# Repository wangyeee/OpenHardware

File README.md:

# OpenHardware
Collections of hardware design related to my drone project.

Brief description for each folders.

| Folder | Description | CAD software |
|---|---|---|
| CurrentMonitor | A simple [ACS758](https://www.allegromicro.com/en/Products/Current-Sensor-ICs/Fifty-To-Two-Hundred-Amp-Integrated-Conductor-Sensor-ICs/ACS758.aspx) breakout board | EAGLE |
| LoRaModem | A board with [Ra-02](http://wiki.ai-thinker.com/_media/lora/docs/c048ps01a1_ra-02_product_specification_v1.1.pdf) LoRa Module and [STM32](https://www.st.com/en/microcontrollers/stm32f103cb.html) MCU | KiCAD |
| OscillatorBreakout | A breakout board for oscillators, supporting three different oscillator packages | KiCAD |
| SimpleFC | Simple yet powerful flight controller for drones, capable of fully autonomous GPS navigation | KiCAD |
| SimpleFCv2 | Version 2 of SimpleFC, with reduced PCB size | KiCAD |
| SimpleFC_G | SimpleFCv2 with integrated GPS receiver | KiCAD |
| MultiRotorHub | A support board in multi-rotor which makes cable management easy | EAGLE |
| PowerModule  | 2s ~ 6s Li-Po BEC with current monitoring |EAGLE  |
| SerialBTBridge | A bridge board between RFM22B telemetry module and HC05 Bluetooth module | EAGLE |
| TinyFC | A tiny flight controller module, supporting board stacking for advanced features | KiCAD |
| ReflowOvenController | A controller board used to convert a commercial oven to PCB reflow oven. | KiCAD |
| AirSensor | A barometer and differential pressure sensor board with UAVCAN support. | KiCAD |
| DIYDummyLoad | A primitive DC dummy load with STM32F103. | EAGLE |
| TinyBEC | 2s ~ 3s / 2A Li-Po BEC, board size 23x18mm. | KiCAD |

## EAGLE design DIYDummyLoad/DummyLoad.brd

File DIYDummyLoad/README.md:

# DIYDummyLoad
A primitive DC dummy load with STM32F103. Firmware is also open source and can be found in this [repo](https://github.com/wangyeee/DIYDummyLoad).

## Components & features
1. STM32F103RC MCU.
2. LMV321 OpAmp and IRFB3607PBF N-channel MOSFET for the load.
3. LMV324 as input buffer for the STM32 ADC.
4. ILI9163C LCD.
5. Rotatory encoder to set parameters.
6. Connector for external voltage sensing.
7. Connector for ESP8266 WiFi module.
8. Temperature sensor and connector for fan control.

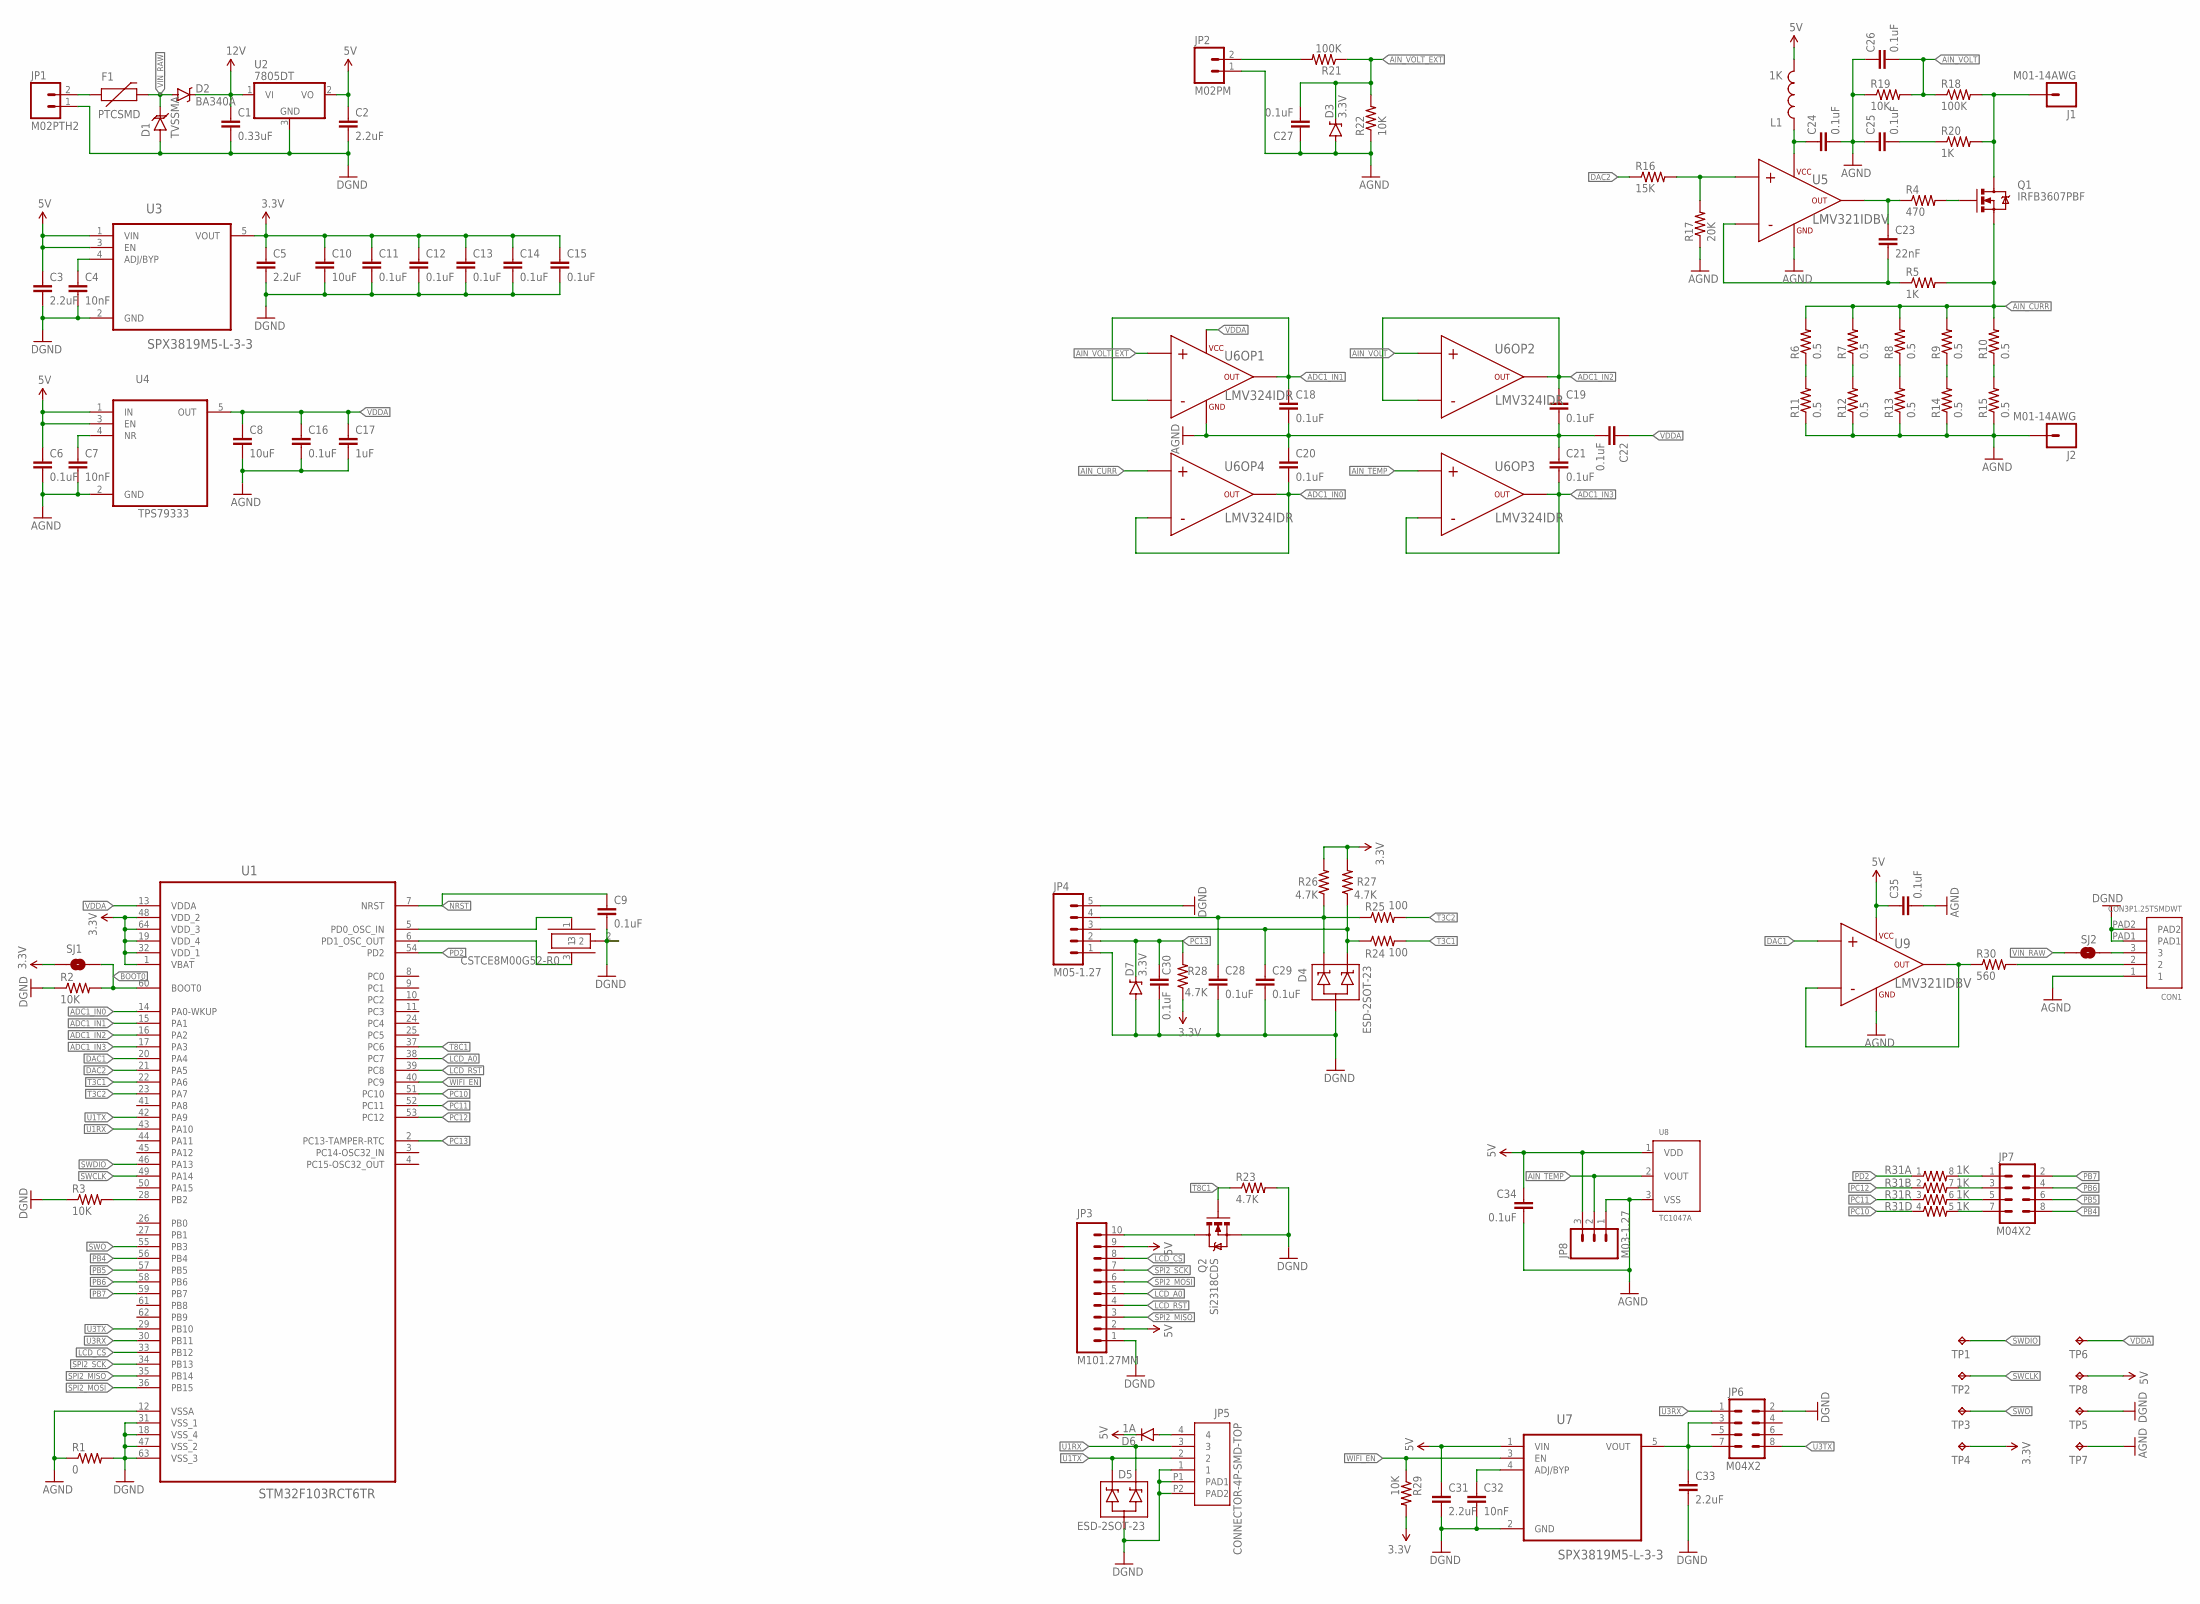
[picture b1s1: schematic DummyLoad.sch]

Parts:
C1: 0.33uF; 0603-CAP
C2, C3, C5, C31, C33: 2.2uF; 0603-CAP
C4, C7, C32: 10nF; 0603-CAP
C6, C9, C11, C12, C13, C14, C15, C16, C18, C19, C20, C21, C22, C24, C25, C26, C27, C28, C29, C30, C34, C35: 0.1uF; 0603-CAP
C8, C10: 10uF; 0603-CAP
C17: 1uF; 0603-CAP
C23: 22nF; 0603-CAP
CON1: CON3P1.25TSMDWT; 1.25T3P
D1: TVSSMA; SMA-DIODE
D2: BA340A; SMA-DIODE
D3, D7: 3.3V; SOD-323
D4, D5: ESD-2SOT-23; SOT23-3
D6: 1A; SOD-123
F1: PTCSMD; PTC-1206
J1, J2: M01-14AWG; PTH1.8MM
JP1: M02PTH2; 1X02_BIG
JP2: M02PM; 1X02_PM
JP3: M101.27MM; 1X10-1.27MM
JP4: M05-1.27; 1X05-1.27MM
JP5: CONNECTOR-4P-SMD-TOP; PH2-4T
JP6, JP7: M04X2; 2X4
JP8: M03-1.27; 1X03-1.27MM
L1: 1K; 0603
Q1: IRFB3607PBF; TO220V
Q2: Si2318CDS; SOT23-3
R1: 0; 0603
R2, R3, R19, R22, R29: 10K; 0603-RES
R4: 470; 0603-RES
R5, R20: 1K; 0603-RES
R6, R7, R8, R9, R10, R11, R12, R13, R14, R15: 0.5; R2512
R16: 15K; 0603-RES
R17: 20K; 0603-RES
R18, R21: 100K; 0603-RES
R23, R26, R27, R28: 4.7K; 0603-RES
R24, R25: 100; 0603-RES
R30: 560; 0603-RES
R31: 1K; 0603-ARV
SJ1: JUMPER-PAD-2-NOYES_SILK; PAD-JUMPER-2-NO_YES_SILK
SJ2: JUMPER-PAD-2-NO; PAD-JUMPER-2-NO_NO_SILK
TP1, TP2, TP3, TP4, TP5, TP6, TP7, TP8: TPB1,27; B1,27
U1: STM32F103RCT6TR; QFP50P1200X1200X160-64N
U2: 7805DT; TO252
U3, U7: SPX3819M5-L-3-3; SOT95P280X145-5N
U4: TPS79333; SOT95P280X145-5N
U5, U9: LMV321IDBV; SOT23-5
U6: LMV324IDR; SOIC14
U8: TC1047A; SOT23
X1: CSTCE8M00G52-R0; CSTCE_M_G

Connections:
3.3V: C5.1, C10.1, C11.1, C12.1, C13.1, C14.1, C15.1, R26.2, R27.2, R28.1, R29.2, SJ1.1, TP4.TP, U1.1 (VBAT), U1.19 (VDD_4), U1.32 (VDD_1), U1.48 (VDD_2), U1.64 (VDD_3), U3.5 (VOUT)
5V: C2.1, C3.1, C6.1, C31.1, C34.1, C35.1, D6.C, JP3.2, JP3.9, JP8.3, L1.2, TP8.TP, U2.2 (VO), U3.1 (VIN), U3.3 (EN), U4.1 (IN), U4.3 (EN), U7.1 (VIN), U8.1 (VDD), U9.5 (VCC+)
12V: C1.1, D2.C, U2.1 (VI)
ADC1_IN0: C20.2, U1.14 (PA0-WKUP), U6.13 (-), U6.14 (OUT)
ADC1_IN1: C18.1, U1.15 (PA1), U6.1 (OUT), U6.2 (-)
ADC1_IN2: C19.1, U1.16 (PA2), U6.6 (-), U6.7 (OUT)
ADC1_IN3: C21.2, U1.17 (PA3), U6.8 (OUT), U6.9 (-)
AGND: C6.2, C7.2, C8.2, C16.2, C17.2, C18.2, C19.2, C20.1, C21.1, C22.2, C24.2, C25.1, C26.1, C27.1, C34.2, C35.2, CON1.1, D3.A, J2.1, JP2.1, JP8.1, R1.1, R11.1, R12.1, R13.1, R14.1, R15.1, R17.1, R19.1, R22.1, TP7.TP, U1.12 (VSSA), U4.2 (GND), U5.2 (GND), U6.11 (GND), U8.3 (VSS), U9.2 (GND)
AIN_CURR: Q1.3 (S), R5.2, R6.2, R7.2, R8.2, R9.2, R10.2, U6.12 (+)
AIN_TEMP: JP8.2, U6.10 (+), U8.2 (VOUT)
AIN_VOLT: C26.2, R18.1, R19.2, U6.5 (+)
AIN_VOLT_EXT: C27.2, D3.C, R21.1, R22.2, U6.3 (+)
BOOT0: R2.2, SJ1.2, U1.60 (BOOT0)
BOOT1: R3.2, U1.28 (PB2)
DAC1: U1.20 (PA4), U9.1 (+)
DAC2: R16.1, U1.21 (PA5)
GND: C1.2, C2.2, C3.2, C4.2, C5.2, C9.2, C10.2, C11.2, C12.2, C13.2, C14.2, C15.2, C28.2, C29.2, C30.2, C31.2, C32.2, C33.2, CON1.PAD1, CON1.PAD2, D1.A, D4.3 (C), D5.3 (C), D7.A, JP1.1, JP3.1, JP4.1, JP4.5, JP5.1, JP5.P1 (PAD1), JP5.P2 (PAD2), JP6.2, Q2.2 (S), R1.2, R2.1, R3.1, R23.2, TP5.TP, U1.18 (VSS_4), U1.31 (VSS_1), U1.47 (VSS_2), U1.63 (VSS_3), U2.3 (GND), U3.2 (GND), U7.2 (GND), X1.2
LCD_A0: JP3.5, U1.38 (PC7)
LCD_CS: JP3.8, U1.33 (PB12)
LCD_RST: JP3.4, U1.39 (PC8)
unnamed: F1.1, JP1.2
unnamed: CON1.3, SJ2.2
unnamed: C4.1, U3.4 (ADJ/BYP)
unnamed: C7.1, U4.4 (NR)
unnamed: JP3.10, Q2.3 (D)
unnamed: U1.5 (PD0_OSC_IN), X1.1
unnamed: U1.6 (PD1_OSC_OUT), X1.3
unnamed: C23.1, R4.1, U5.4 (OUT)
unnamed: Q1.1 (G), R4.2
unnamed: C25.2, R20.1
unnamed: C23.2, R5.1, U5.3 (-)
unnamed: R6.1, R11.2
unnamed: R7.1, R12.2
unnamed: R8.1, R13.2
unnamed: R9.1, R14.2
unnamed: R10.1, R15.2
unnamed: R16.2, R17.2, U5.1 (+)
unnamed: C29.1, D4.2 (A2), JP4.3, R24.1, R27.1
unnamed: JP2.2, R21.2
unnamed: C24.1, L1.1, U5.5 (VCC+)
unnamed: C28.1, D4.1 (A1), JP4.4, R25.1, R26.1
unnamed: D6.A, JP5.4
unnamed: C33.1, JP6.3, JP6.7, U7.5 (VOUT)
unnamed: C32.1, U7.4 (ADJ/BYP)
unnamed: R30.1, U9.3 (-), U9.4 (OUT)
unnamed: CON1.2, R30.2
unnamed: JP7.1, R31.8 (2)
unnamed: JP7.3, R31.7 (2)
unnamed: JP7.5, R31.6 (2)
unnamed: JP7.7, R31.5 (2)
NRST: C9.1, U1.7 (NRST)
PB4: JP7.8, U1.56 (PB4)
PB5: JP7.6, U1.57 (PB5)
PB6: JP7.4, U1.58 (PB6)
PB7: JP7.2, U1.59 (PB7)
PC10: R31.4 (1), U1.51 (PC10)
PC11: R31.3 (1), U1.52 (PC11)
PC12: R31.2 (1), U1.53 (PC12)
PC13: C30.1, D7.C, JP4.2, R28.2, U1.2 (PC13-TAMPER-RTC)
PD2: R31.1, U1.54 (PD2)
SPI2_MISO: JP3.3, U1.35 (PB14)
SPI2_MOSI: JP3.6, U1.36 (PB15)
SPI2_SCK: JP3.7, U1.34 (PB13)
SWCLK: TP2.TP, U1.49 (PA14)
SWDIO: TP1.TP, U1.46 (PA13)
SWO: TP3.TP, U1.55 (PB3)
T3C1: R24.2, U1.22 (PA6)
T3C2: R25.2, U1.23 (PA7)
T8C1: Q2.1 (G), R23.1, U1.37 (PC6)
U1RX: D5.1 (A1), JP5.3, U1.43 (PA10)
U1TX: D5.2 (A2), JP5.2, U1.42 (PA9)
U3RX: JP6.1, U1.30 (PB11)
U3TX: JP6.8, U1.29 (PB10)
VDDA: C8.1, C16.1, C17.1, C22.1, TP6.TP, U1.13 (VDDA), U4.5 (OUT), U6.4 (VCC+)
VIN_RAW: D1.C, D2.A, F1.2, SJ2.1
V_LOAD: J1.1, Q1.2 (D), R18.2, R20.2
WIFI_EN: R29.1, U1.40 (PC9), U7.3 (EN)

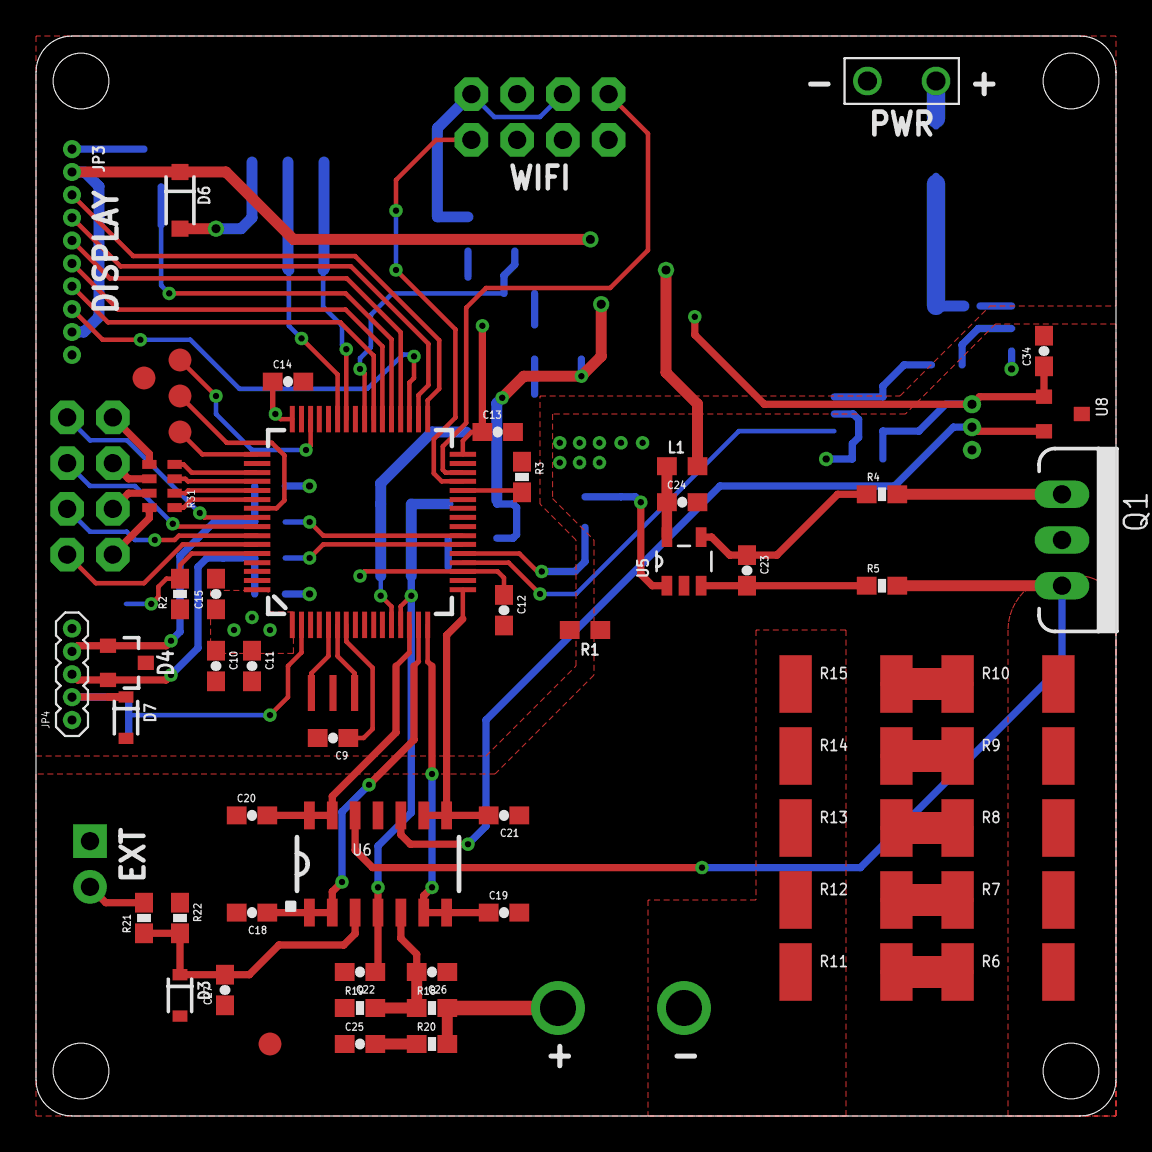
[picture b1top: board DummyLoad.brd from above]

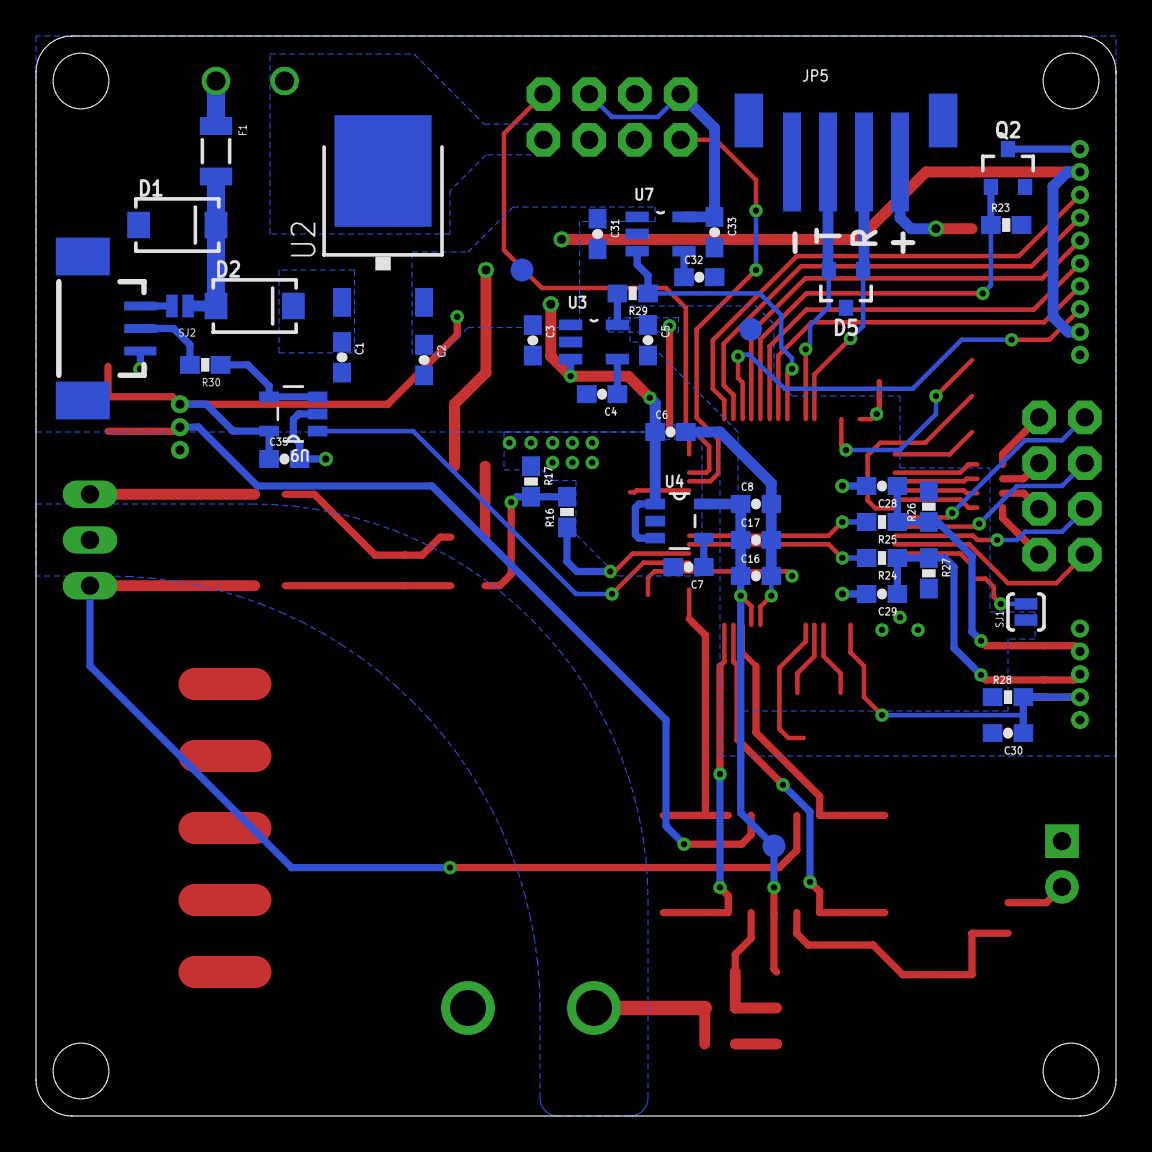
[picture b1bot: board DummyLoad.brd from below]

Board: 2 copper layers, 60.0 x 60.0 mm, 108 parts (44 on the bottom side), 77 nets.

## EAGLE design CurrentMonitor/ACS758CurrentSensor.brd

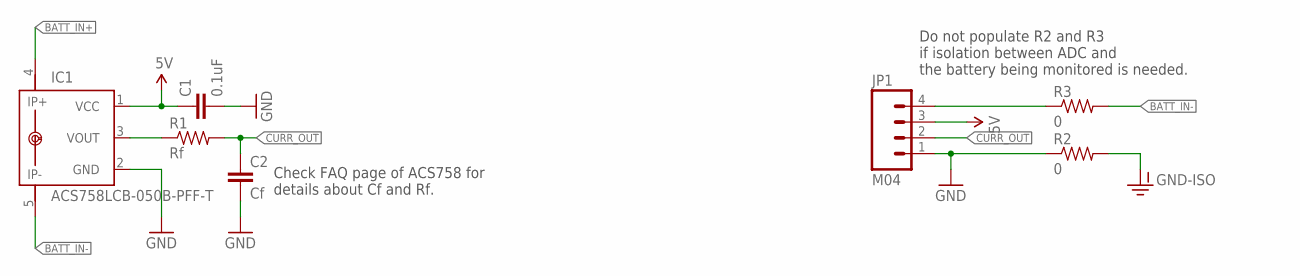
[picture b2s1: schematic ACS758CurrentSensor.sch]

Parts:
C1: 0.1uF; 0603-CAP
C2: Cf; 0603-CAP
IC1: ACS758LCB-050B-PFF-T; CB-PFF
JP1: M04; 1X04
R1: Rf; 0603
R2, R3: 0; 0603

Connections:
5V: C1.1, IC1.1 (VCC), JP1.3
BATT_IN+: IC1.4 (IP+)
BATT_IN-: IC1.5 (IP-), R3.2
CURR_OUT: C2.1, JP1.2, R1.2
GND: C1.2, C2.2, IC1.2 (GND), JP1.1, R2.1
GND-ISO: R2.2
unnamed: IC1.3 (VOUT), R1.1
unnamed: JP1.4, R3.1

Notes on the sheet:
Do not populate R2 and R3 if isolation between ADC and the battery being monitored is needed.
Check FAQ page of ACS758 for details about Cf and Rf.

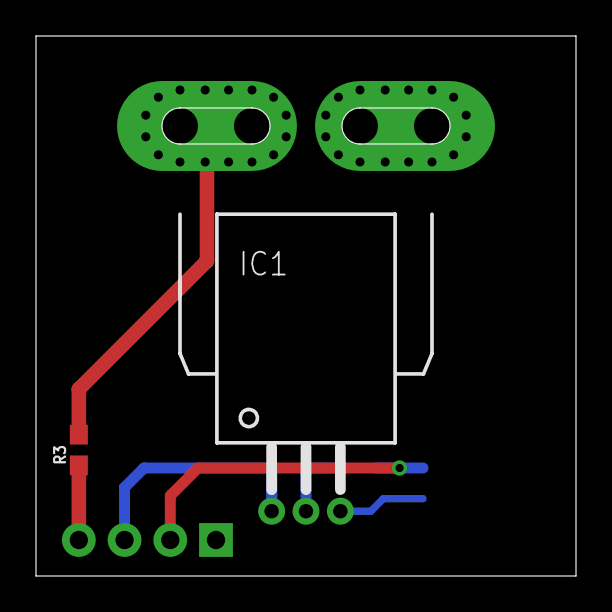
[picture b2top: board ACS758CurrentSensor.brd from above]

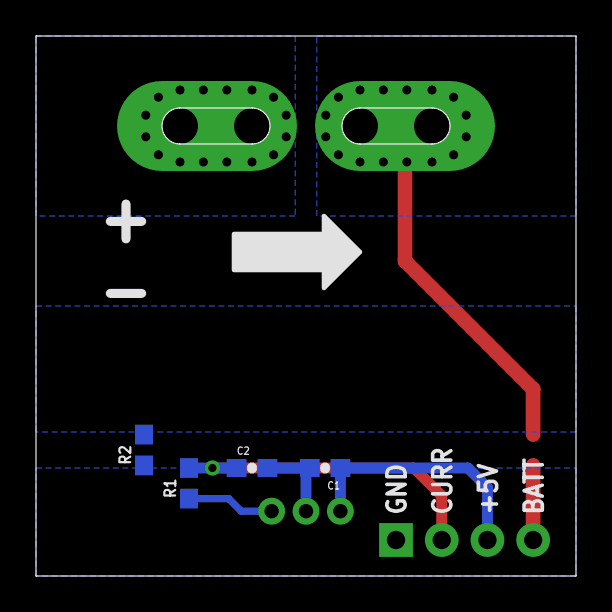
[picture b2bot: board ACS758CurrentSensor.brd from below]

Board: 2 copper layers, 30.0 x 30.0 mm, 7 parts (4 on the bottom side), 6 nets.

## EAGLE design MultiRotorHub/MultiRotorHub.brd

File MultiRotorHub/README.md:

# Multi rotor Hub
Up to 8 motors supported. M7 and M8 input can also be used to drive LEDs.
On board UBEC supported up to 8s Li-po and 5V/3A output.

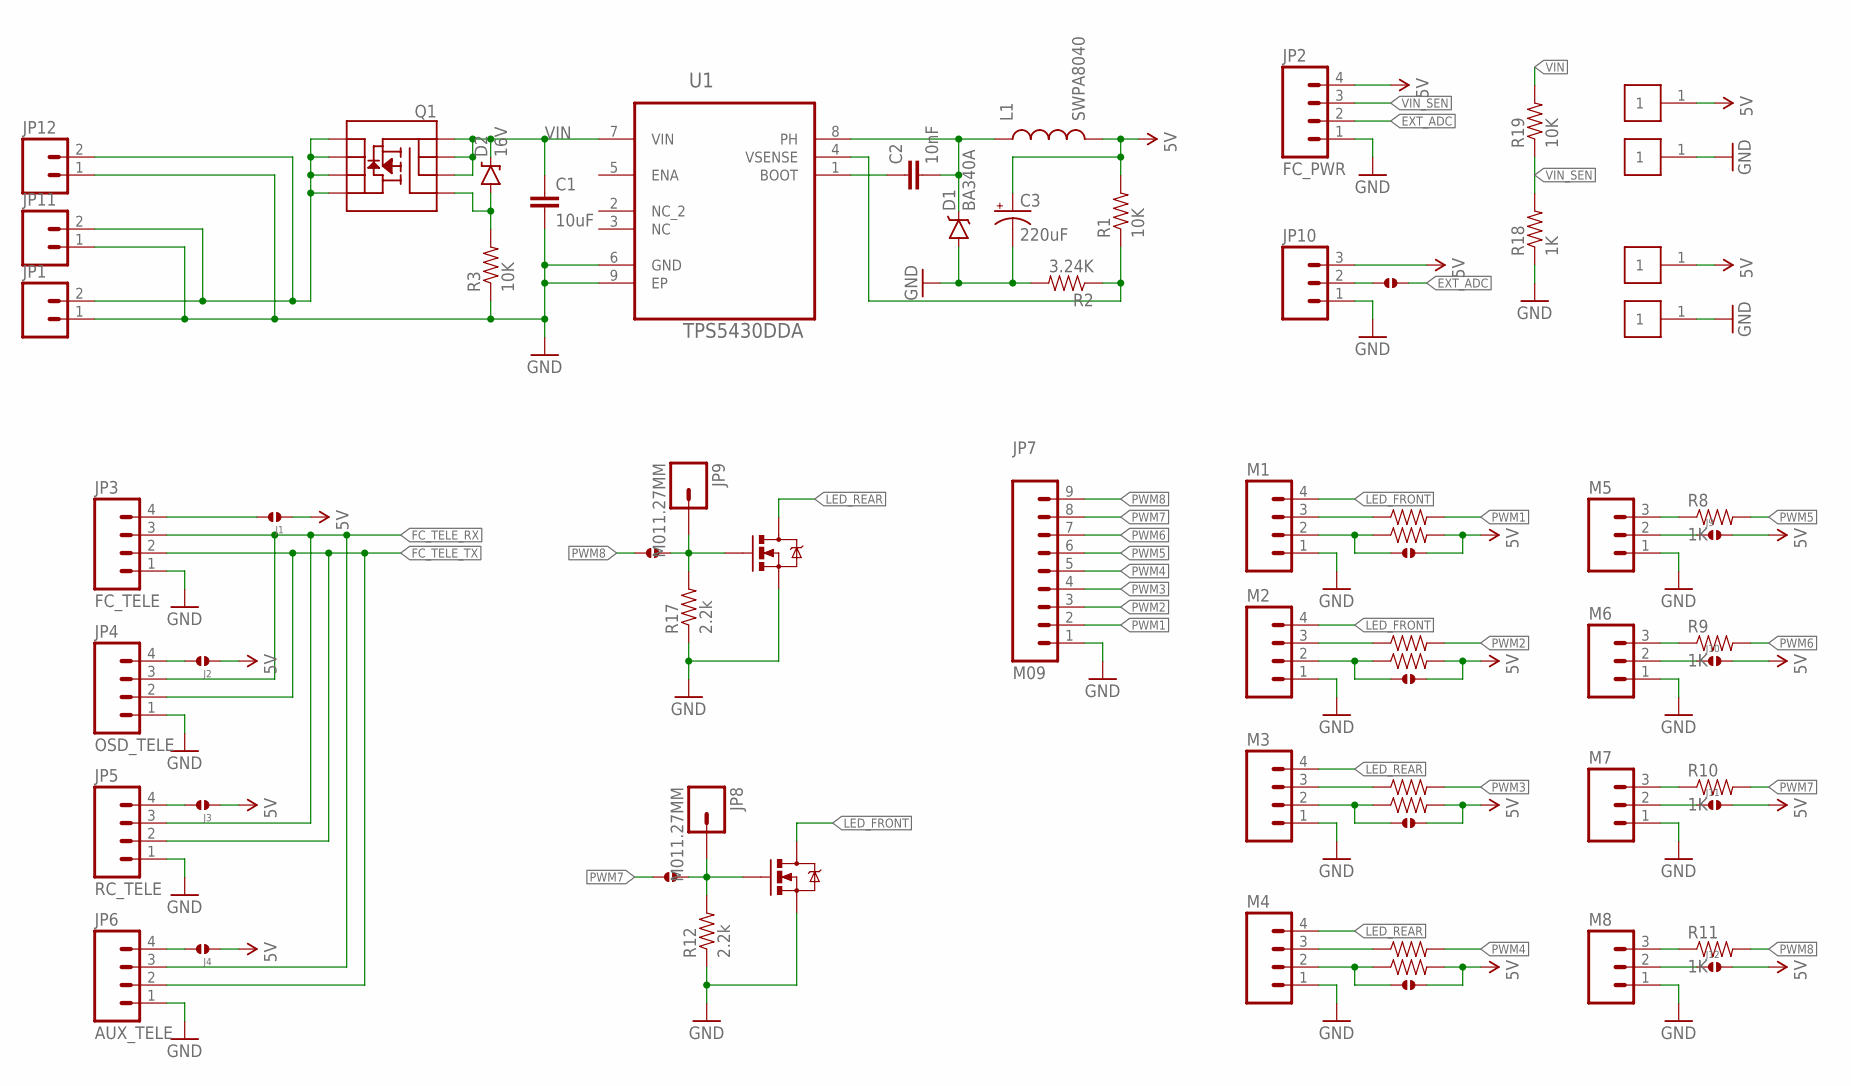
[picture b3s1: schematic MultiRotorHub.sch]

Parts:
C1: 10uF; 1206
C2: 10nF; 0603-CAP
C3: 220uF; PANASONIC_D
CON1, CON2, CON3, CON4: CON1P2.54MM; SMD2.54MM
D1: BA340A; SMA-DIODE
D2: 16V; SOD-123
J1, J2, J3, J4, J5, J6, J7, J8, J9, J10, J11, J12, J13, J14, J15: SOLDERJUMPER.2.MED; 2.MED
JP1, JP11, JP12: M02PTH; 1X02
JP2: FC_PWR; 1X04-1.27MM
JP3: FC_TELE; 1X04-1.27MM
JP4: OSD_TELE; 1X04-1.27MM
JP5: RC_TELE; 1X04-1.27MM
JP6: AUX_TELE; 1X04-1.27MM
JP7: M09; 1X09
JP8, JP9: M011.27MM; 1X01-1.27MM
JP10: M03M03-1.27MM; 1X03-1.27MM
L1: SWPA8040; INC8040
M1, M2, M3, M4: M04PTH; 1X04
M5, M6, M7, M8: M03PTH; 1X03
Q1: MOSFET-PCHANNEL-SOIC8SOIC8; SO08
Q2, Q3: MOSFET-NCHANNELBSS123LT1G; SOT23-3
R1, R3, R19: 10K; 0603-RES
R2: 3.24K; 0603-RES
R4, R5, R6, R7, R8, R9, R10, R11, R18: 1K; 0603-RES
R12, R17: 2.2k; 0603-RES
R13, R14, R15, R16: 10; R2512
U1: TPS5430DDA; SOIC127P600X170-9N

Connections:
5V: C3.+, CON1.1, CON3.1, J1.1, J2.1, J3.1, J4.1, J5.2, J6.2, J7.2, J8.2, J9.2, J10.2, J11.2, J12.2, JP2.4, JP10.3, L1.2, R1.2, R13.2, R14.2, R15.2, R16.2
EXT_ADC: J15.2, JP2.2
FC_TELE_RX: JP3.3, JP4.3, JP5.3, JP6.3
FC_TELE_TX: JP3.2, JP4.2, JP5.2, JP6.2
GND: C1.2, C3.-, CON2.1, CON4.1, D1.A, JP1.1, JP2.1, JP3.1, JP4.1, JP5.1, JP6.1, JP7.1, JP10.1, JP11.1, JP12.1, M1.1, M2.1, M3.1, M4.1, M5.1, M6.1, M7.1, M8.1, Q2.2 (S), Q3.2 (S), R2.2, R3.1, R12.1, R17.1, R18.1, U1.6 (GND), U1.9 (EP)
LED_FRONT: M1.4, M2.4, Q2.3 (D)
LED_REAR: M3.4, M4.4, Q3.3 (D)
unnamed: C2.1, U1.1 (BOOT)
unnamed: J1.2, JP3.4
unnamed: R1.1, R2.1, U1.4 (VSENSE)
unnamed: D2.A, Q1.4 (G), R3.2
unnamed: J3.2, JP5.4
unnamed: J4.2, JP6.4
unnamed: J2.2, JP4.4
unnamed: J5.1, M1.2, R13.1
unnamed: M1.3, R4.1
unnamed: J6.1, M2.2, R14.1
unnamed: M2.3, R5.1
unnamed: J7.1, M3.2, R15.1
unnamed: M3.3, R6.1
unnamed: J8.1, M4.2, R16.1
unnamed: M4.3, R7.1
unnamed: J9.1, M5.2
unnamed: M5.3, R8.1
unnamed: J10.1, M6.2
unnamed: M6.3, R9.1
unnamed: J11.1, M7.2
unnamed: M7.3, R10.1
unnamed: J12.1, M8.2
unnamed: M8.3, R11.1
unnamed: J13.2, JP8.1, Q2.1 (G), R12.2
unnamed: J14.2, JP9.1, Q3.1 (G), R17.2
unnamed: J15.1, JP10.2
PWM1: JP7.2, R4.2
PWM2: JP7.3, R5.2
PWM3: JP7.4, R6.2
PWM4: JP7.5, R7.2
PWM5: JP7.6, R8.2
PWM6: JP7.7, R9.2
PWM7: J13.1, JP7.8, R10.2
PWM8: J14.1, JP7.9, R11.2
VIN: C1.1, D2.C, Q1.1 (S), Q1.2 (S), Q1.3 (S), R19.2, U1.7 (VIN)
VIN_SEN: JP2.3, R18.2, R19.1
V_BATT: JP1.2, JP11.2, JP12.2, Q1.5 (D), Q1.6 (D), Q1.7 (D), Q1.8 (D)
V_OUT: C2.2, D1.C, L1.1, U1.8 (PH)

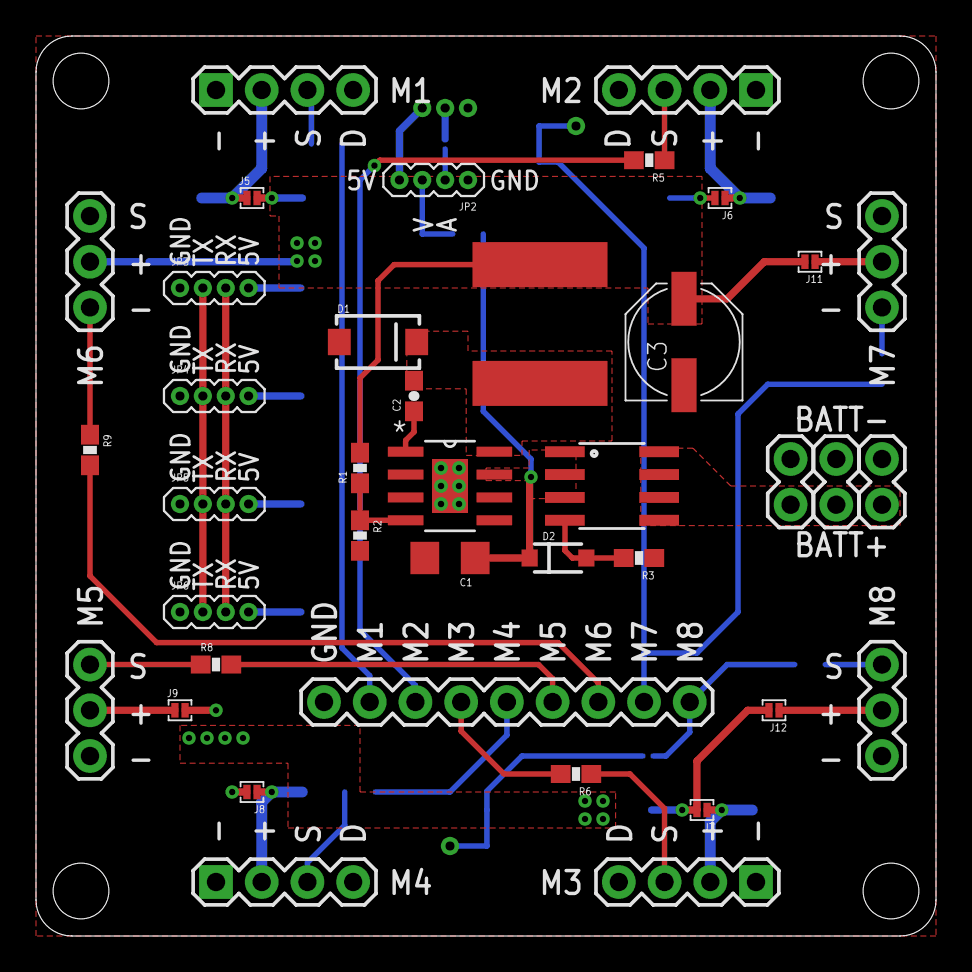
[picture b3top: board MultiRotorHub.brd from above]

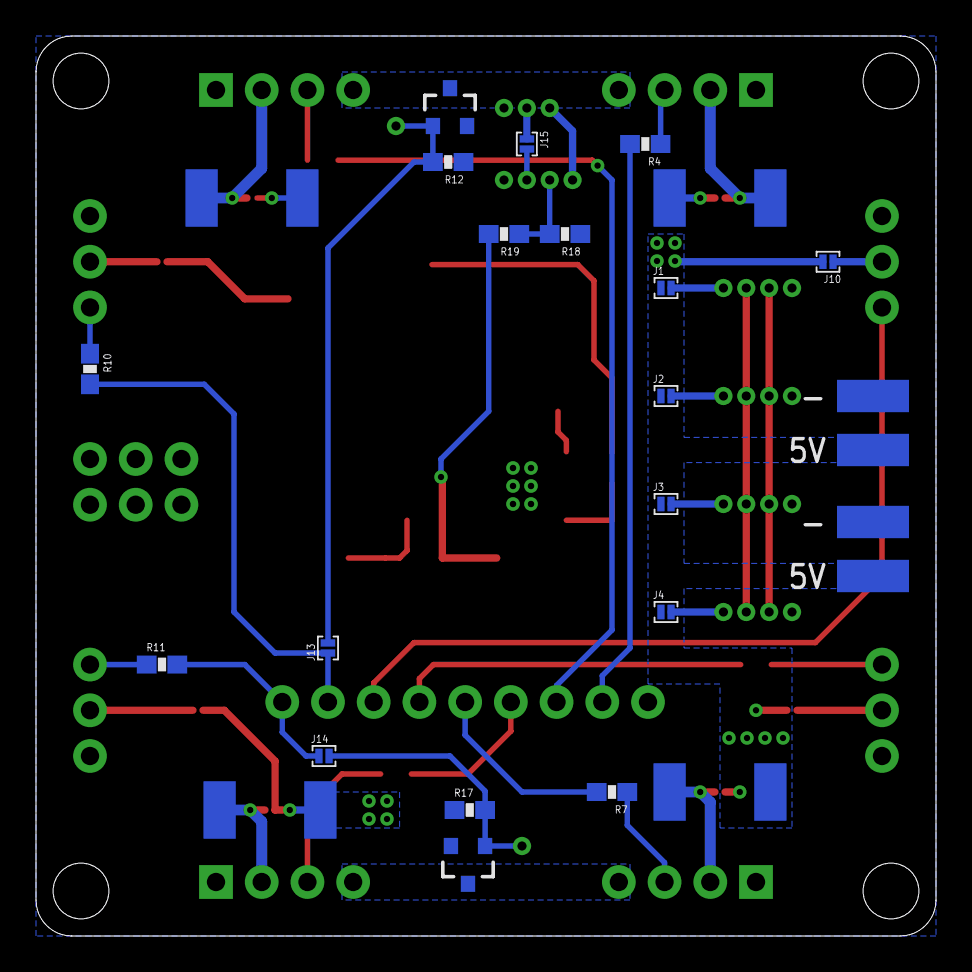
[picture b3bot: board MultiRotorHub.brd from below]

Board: 2 copper layers, 50.0 x 50.0 mm, 68 parts (26 on the bottom side), 45 nets.

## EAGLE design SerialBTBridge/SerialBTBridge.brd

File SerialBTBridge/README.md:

# Serial to Bluetooth Bridge

Relays serial data from RFM22B to HC05 bluetooth module. No need for USB OTG cable when using with Android ground stations.

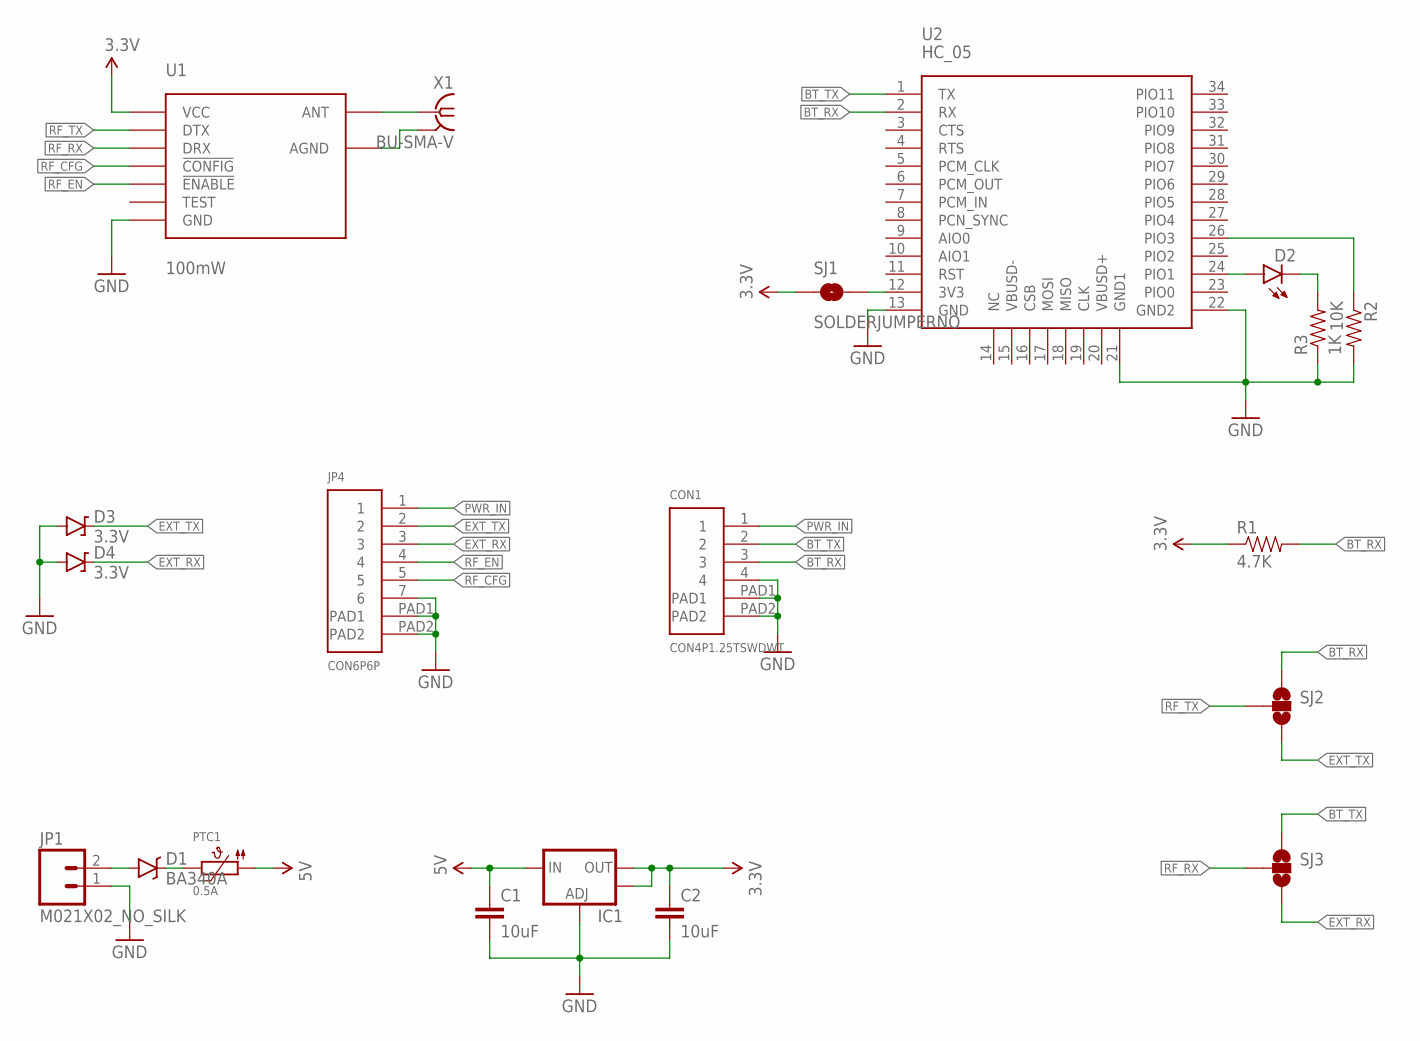
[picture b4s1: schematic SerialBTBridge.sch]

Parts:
C1: 10uF; 0805-CAP
C2: 10uF; 0603-CAP
CON1: CON4P1.25TSWDWT; 1.25T4P
D1: BA340A; SMA-DIODE
D2: LED0603; LED-0603
D3, D4: 3.3V; SOD-323
IC1: V_REG_LM1117SOT223; SOT223
JP1: M021X02_NO_SILK; 1X02_NO_SILK
JP4: CON6P6P; 1.25T6P
PTC1: 0.5A; PTC1812
R1: 4.7K; 0603-RES
R2: 10K; 0603-RES
R3: 1K; 0603-RES
SJ1: SOLDERJUMPERNO; SJ_2S-NO
SJ2, SJ3: SOLDERJUMPER_2WAYS; SJ_3
U1: 100mW; HM-TRP-SMD
U2: HC_05; BLUETOOTH_SMD
X1: BU-SMA-V

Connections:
3.3V: C2.1, IC1.2 (OUT), IC1.4 (OUT), R1.1, SJ1.1, U1.VCC
5V: C1.P$1 (1), IC1.3 (IN), PTC1.P$1 (1)
ANT_GND: U1.AGND, X1.2, X1.3 (2), X1.4 (2), X1.5 (2)
BT_RX: CON1.3, R1.2, SJ2.1, U2.2 (RX)
BT_TX: CON1.2, SJ3.1, U2.1 (TX)
EXT_RX: D4.C, JP4.3, SJ3.3
EXT_TX: D3.C, JP4.2, SJ2.3
GND: C1.P$2 (2), C2.2, CON1.4, CON1.PAD1, CON1.PAD2, D3.A, D4.A, IC1.1 (ADJ), JP1.1, JP4.7 (6), JP4.PAD1, JP4.PAD2, R2.2, R3.1, U1.GND, U2.13 (GND), U2.21 (GND1), U2.22 (GND2)
unnamed: U1.ANT, X1.1
unnamed: SJ1.2, U2.12 (3V3)
unnamed: R2.1, U2.26 (PIO3)
unnamed: D1.C, PTC1.P$2 (2)
unnamed: D2.A, U2.24 (PIO1)
unnamed: D2.C, R3.2
PWR_IN: CON1.1, D1.A, JP1.2, JP4.1
RF_CFG: JP4.5, U1.!CONFIG
RF_EN: JP4.4, U1.!ENABLE
RF_RX: SJ3.2, U1.DRX
RF_TX: SJ2.2, U1.DTX

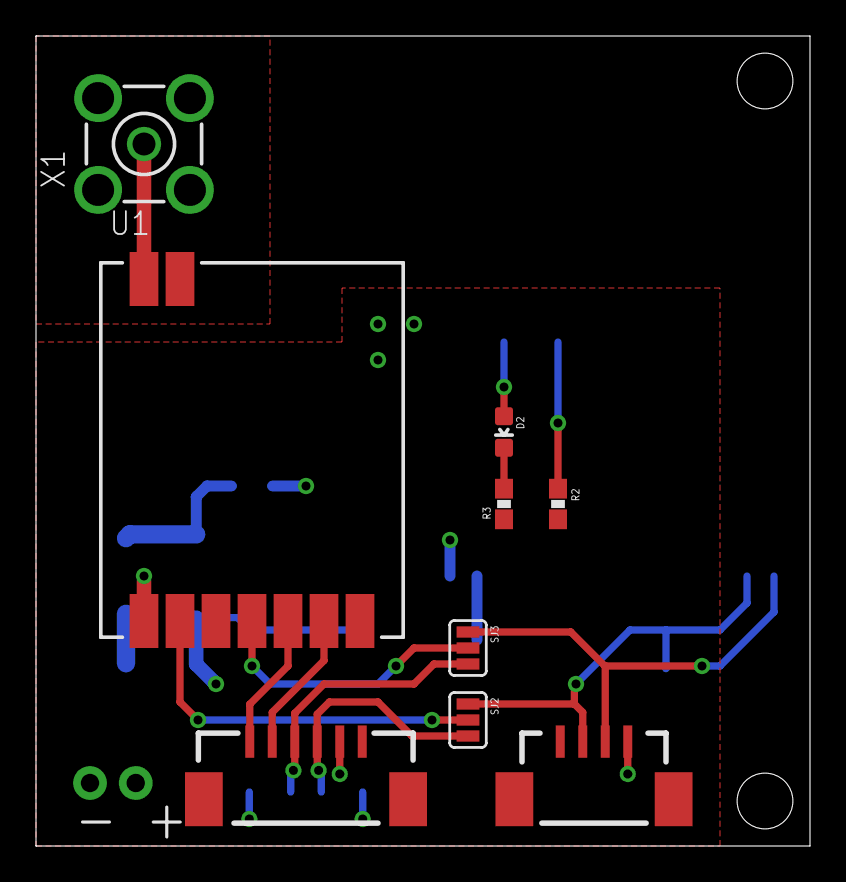
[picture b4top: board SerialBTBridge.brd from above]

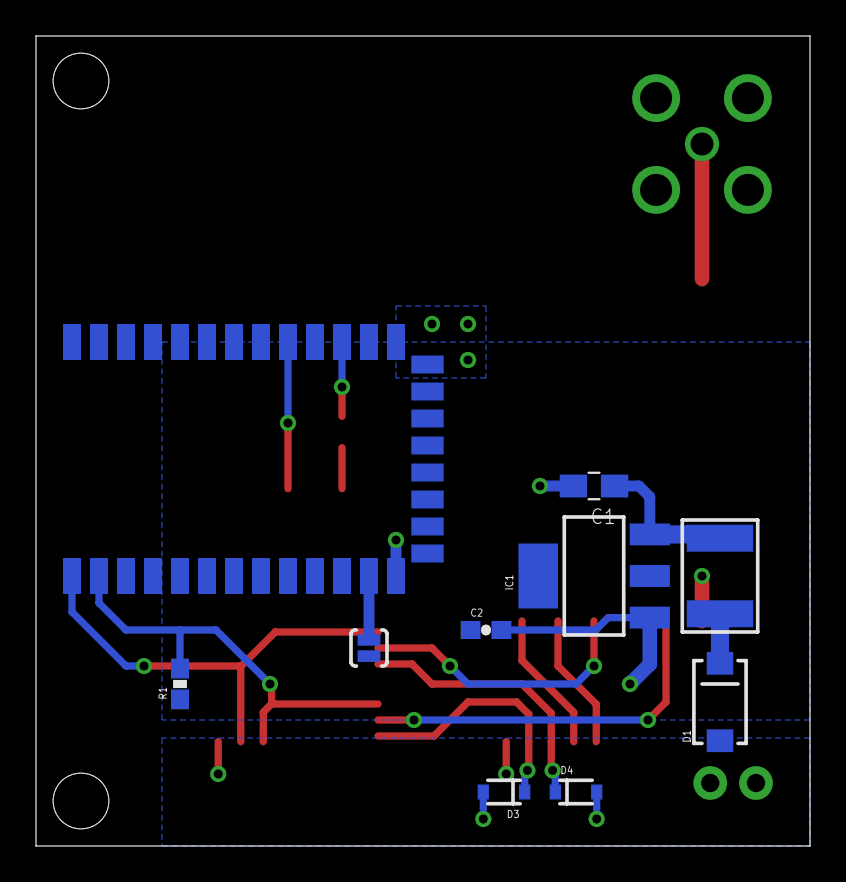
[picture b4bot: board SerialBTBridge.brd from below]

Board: 2 copper layers, 43.0 x 45.0 mm, 20 parts (10 on the bottom side), 19 nets.

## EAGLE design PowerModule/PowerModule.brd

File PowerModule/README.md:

# Power Module

UBEC and vlotage/current monitor, can be powered from 2s to 6s LiPo batteries.

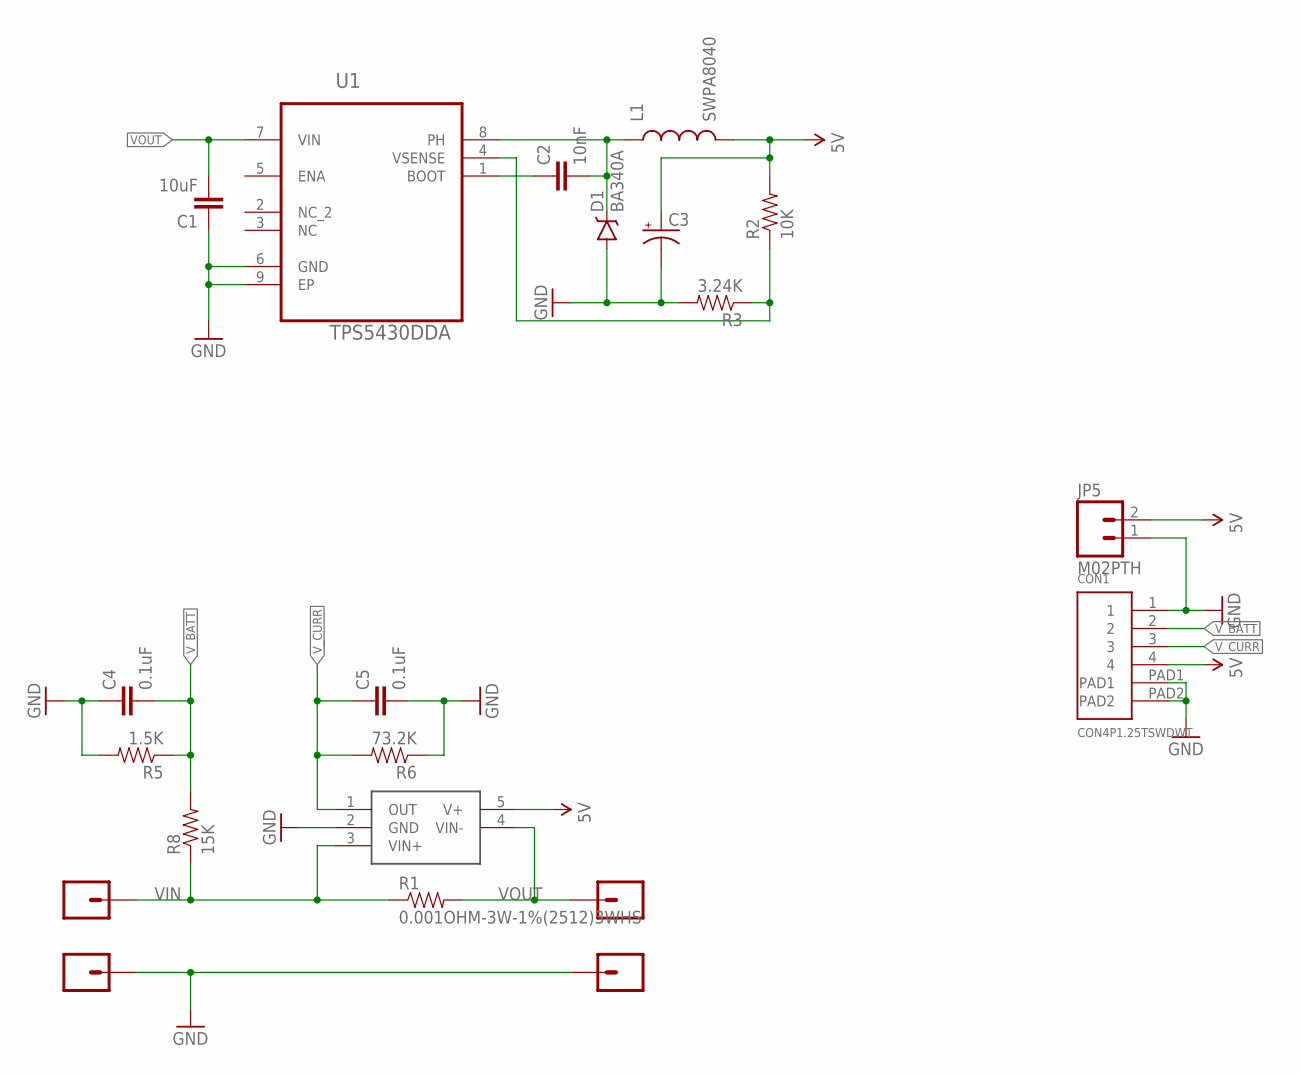
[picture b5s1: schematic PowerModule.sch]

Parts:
C1: 10uF; 1206
C2: 10nF; 0603-CAP
C3: CAP_POLD; PANASONIC_D
C4, C5: 0.1uF; 0603-CAP
CON1: CON4P1.25TSWDWT; 1.25T4P
D1: BA340A; SMA-DIODE
JP1, JP2, JP3, JP4: M016.5X5.5; 1PAD
JP5: M02PTH; 1X02
L1: SWPA8040; INC8040
R1: 0.001OHM-3W-1%(2512)3WHS; R2512W
R2: 10K; 0603-RES
R3: 3.24K; 0603-RES
R5: 1.5K; 0603
R6: 73.2K; 0603-RES
R8: 15K; 0603-RES
U1: TPS5430DDA; SOIC127P600X170-9N
U$1: INA169; SOT23-5

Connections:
5V: C3.+, CON1.4, JP5.2, L1.2, R2.2, U$1.5 (V+)
GND: C1.1, C3.-, C4.1, C5.2, CON1.1, CON1.PAD1, CON1.PAD2, D1.A, JP3.1, JP4.1, JP5.1, R3.2, R5.2, R6.1, U1.6 (GND), U1.9 (EP), U$1.2 (GND)
INCT: C2.2, D1.C, L1.1, U1.8 (PH)
unnamed: C2.1, U1.1 (BOOT)
unnamed: R2.1, R3.1, U1.4 (VSENSE)
VIN: JP1.1, R1.1, R8.1, U$1.3 (VIN+)
VOUT: C1.2, JP2.1, R1.2, U1.7 (VIN), U$1.4 (VIN-)
V_BATT: C4.2, CON1.2, R5.1, R8.2
V_CURR: C5.1, CON1.3, R6.2, U$1.1 (OUT)

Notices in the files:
parts and their libraries:
SparkFun-Capacitors: Licensing: Creative Commons ShareAlike 4.0 International - https://creativecommons.org/licenses/by-sa/4.0
microbuilder: This work is placed in the public domain, and may be freely used for commercial and non-commercial work with the following conditions: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
